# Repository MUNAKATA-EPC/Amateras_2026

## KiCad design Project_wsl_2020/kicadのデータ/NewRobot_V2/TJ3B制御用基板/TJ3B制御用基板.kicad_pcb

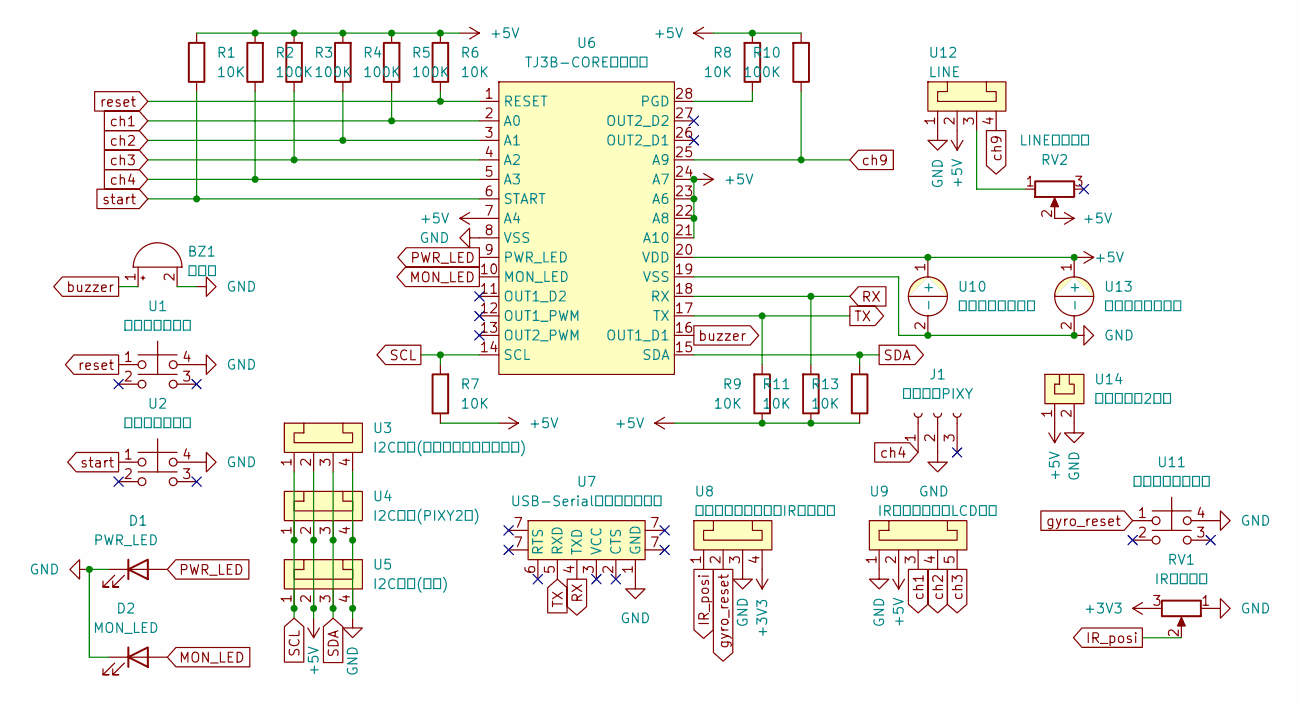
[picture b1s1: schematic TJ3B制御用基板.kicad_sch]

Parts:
BZ1: ブザー
D1: PWR_LED; PinSocket_1x02_P2.54mm_Vertical
D2: MON_LED; PinSocket_1x02_P2.54mm_Vertical
J1: カメラ用PIXY; PinSocket_1x03_P2.54mm_Vertical
R1, R6, R7, R8, R9, R11, R13: 10K; 抵抗
R2, R3, R4, R5, R10: 100K; 抵抗
RV1: IR可変抵抗; Potentiometer
RV2: LINE可変抵抗; Potentiometer
U1: リセットボタン; タクトスイッチ
U2: スタートボタン; タクトスイッチ
U3: I2Cピン(モータードライバー用); L字コネクター4ピン
U4: I2Cピン(PIXY2用); コネクター4ピン
U5: I2Cピン(予備); コネクター4ピン
U6: TJ3B-COREマイコン
U7: USB-Serial変換アダプター
U8: ジャイロリセット・IR可変抵抗; コネクター4ピン
U9: IR・ジャイロ・LCD基盤; L字コネクター5ピン
U10, U13: 電解コンデンサー
U11: ジャイロリセット; タクトスイッチ
U12: LINE; L字コネクター4ピン
U14: コネクター2ピン; L字コネクター2ピン

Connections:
+3V3: RV1.3, U8.4
+5V: R1.2, R2.2, R3.2, R4.2, R5.2, R6.2, R7.1, R8.2, R9.1, R10.2, R11.1, R13.1, RV2.2, U3.2, U4.2, U5.2, U6.7 (A4), U6.20 (VDD), U6.21 (A10), U6.22 (A8), U6.23 (A6), U6.24 (A7), U9.2, U10.1 (+), U12.2, U13.1 (+), U14.1
GND: BZ1.2 (+), D1.1 (K), D2.1 (K), J1.2, RV1.1, U1.4, U2.4, U3.4, U4.4, U5.4, U6.8 (VSS), U6.19 (VSS), U7.1 (GND), U8.3, U9.1, U10.2 (-), U11.4, U12.1, U13.2 (-), U14.2
IR_posi: RV1.2, U8.1
MON_LED: D2.2 (A), U6.10 (MON_LED)
unnamed: R8.1, U6.28 (PGD)
unnamed: RV2.1, U12.3
PWR_LED: D1.2 (A), U6.9 (PWR_LED)
RX: R11.2, U6.18 (RX), U7.4 (TXD)
SCL: R7.2, U3.1, U4.1, U5.1, U6.14 (SCL)
SDA: R13.2, U3.3, U4.3, U5.3, U6.15 (SDA)
TX: R9.2, U6.17 (TX), U7.5 (RXD)
buzzer: BZ1.1 (-), U6.16 (OUT1_D1)
ch1: R5.1, U6.2 (A0), U9.3
ch2: R4.1, U6.3 (A1), U9.4
ch3: R3.1, U6.4 (A2), U9.5
ch4: J1.1, R2.1, U6.5 (A3)
ch9: R10.1, U6.25 (A9), U12.4
gyro_reset: U8.2, U11.1
reset: R6.1, U1.1, U6.1 (RESET)
start: R1.1, U2.1, U6.6 (START)

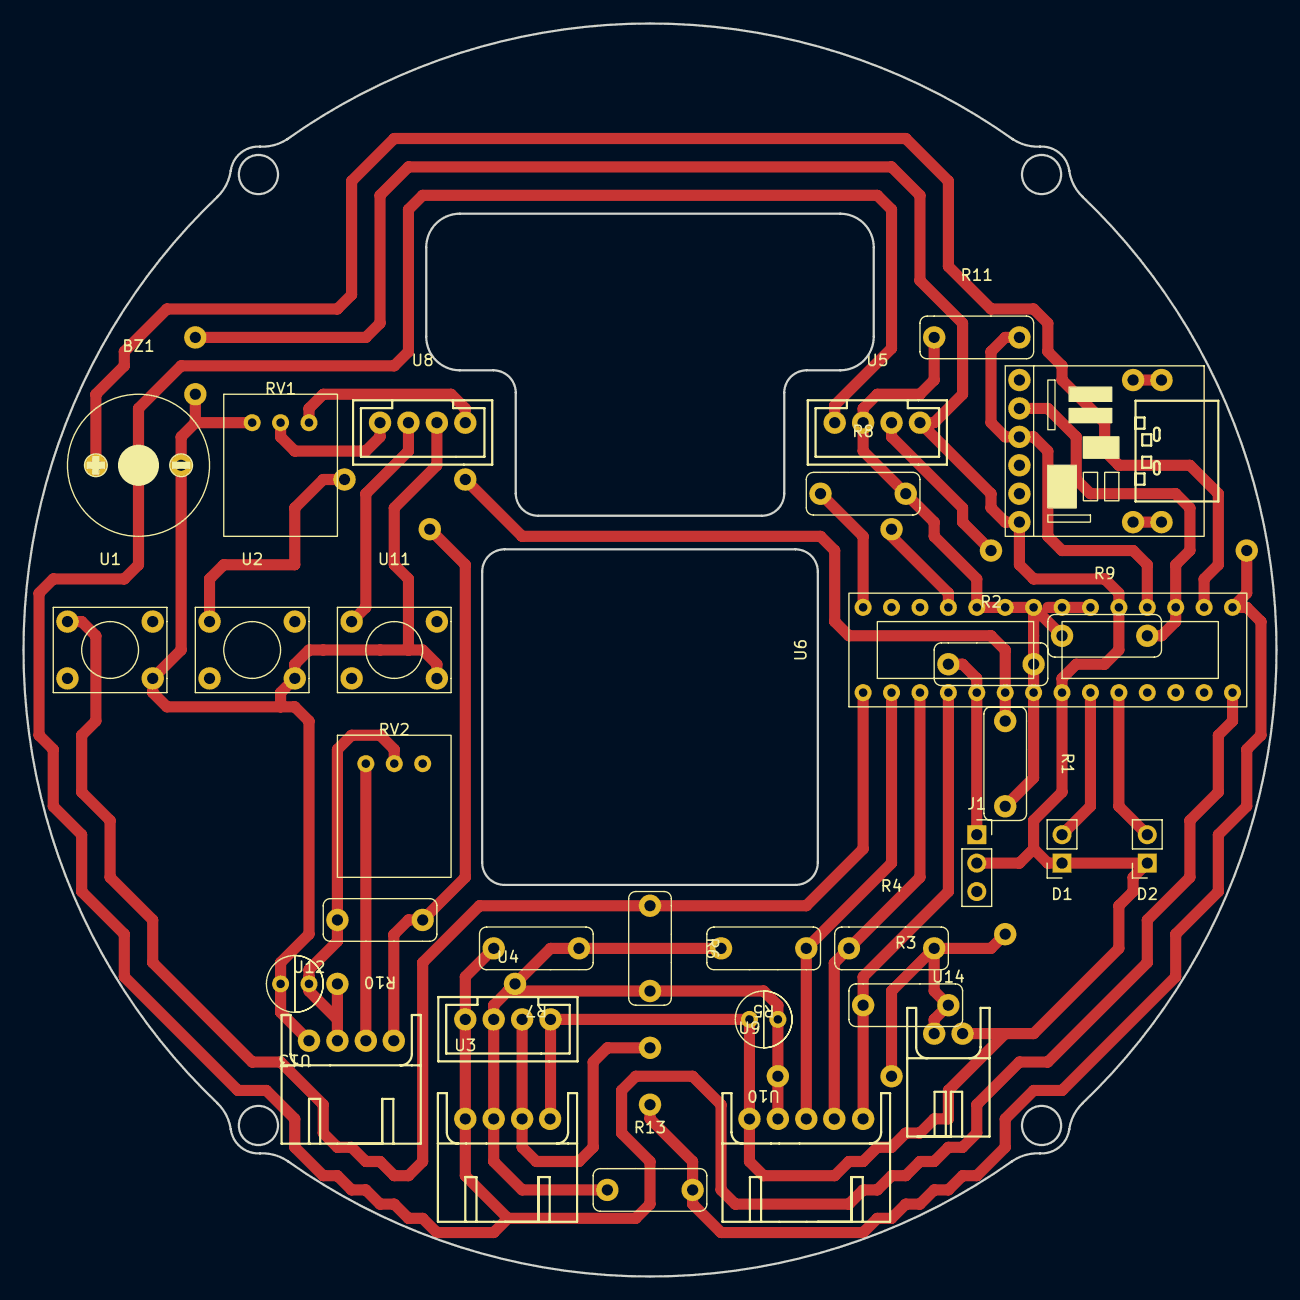
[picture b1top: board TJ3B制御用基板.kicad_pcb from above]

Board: 2 copper layers, 112.0 x 112.0 mm, 32 parts (0 on the bottom side), 21 nets.

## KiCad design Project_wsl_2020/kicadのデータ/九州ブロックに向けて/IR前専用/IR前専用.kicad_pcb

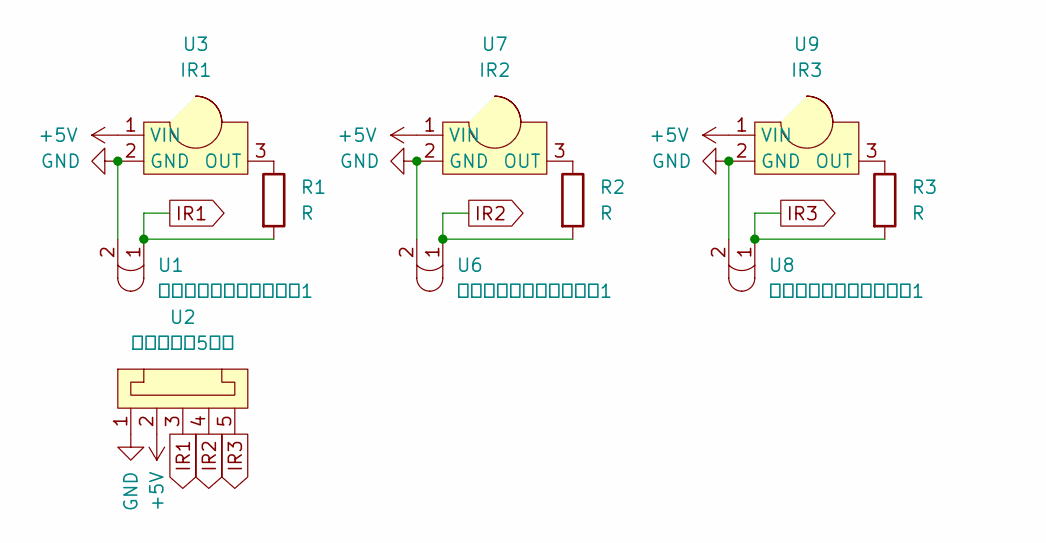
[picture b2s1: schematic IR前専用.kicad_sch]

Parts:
R1, R2, R3: R; 抵抗
U1, U6, U8: セラミックコンデンサー1; セラミックコンデンサー
U2: コネクター5ピン
U3: IR1; IR素子
U7: IR2; IR素子
U9: IR3; IR素子

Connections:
+5V: U2.2, U3.1 (VIN), U7.1 (VIN), U9.1 (VIN)
GND: U1.2, U2.1, U3.2 (GND), U6.2, U7.2 (GND), U8.2, U9.2 (GND)
IR1: R1.2, U1.1, U2.3
IR2: R2.2, U2.4, U6.1
IR3: R3.2, U2.5, U8.1
unnamed: R1.1, U3.3 (OUT)
unnamed: R2.1, U7.3 (OUT)
unnamed: R3.1, U9.3 (OUT)

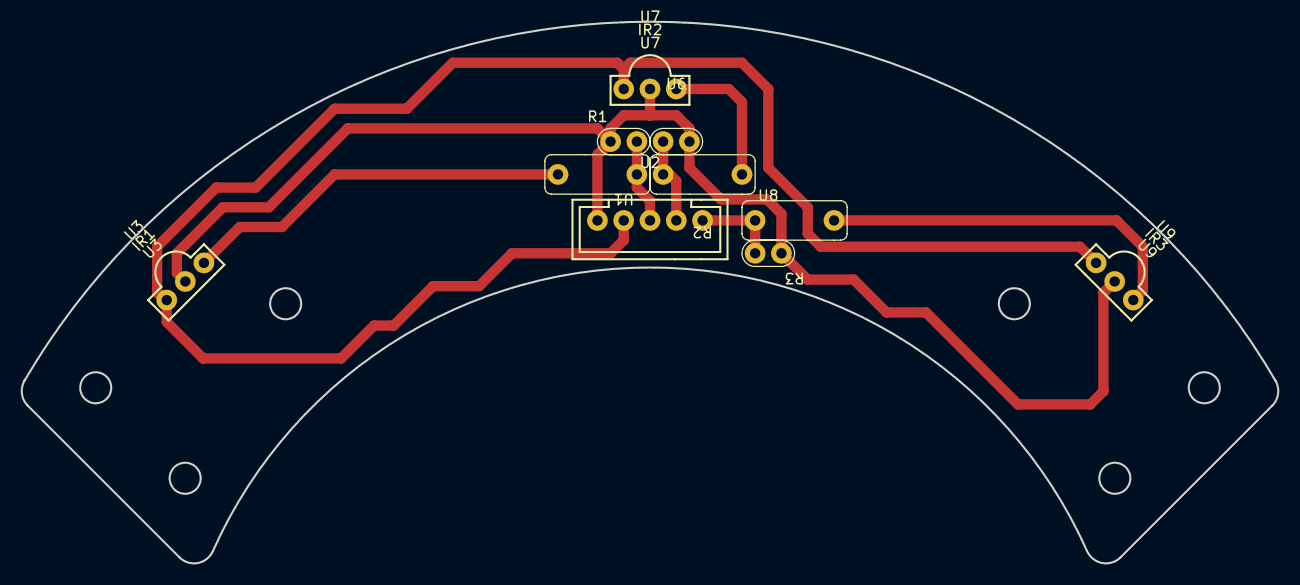
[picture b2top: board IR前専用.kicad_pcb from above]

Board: 2 copper layers, 121.4 x 52.3 mm, 10 parts (0 on the bottom side), 8 nets.

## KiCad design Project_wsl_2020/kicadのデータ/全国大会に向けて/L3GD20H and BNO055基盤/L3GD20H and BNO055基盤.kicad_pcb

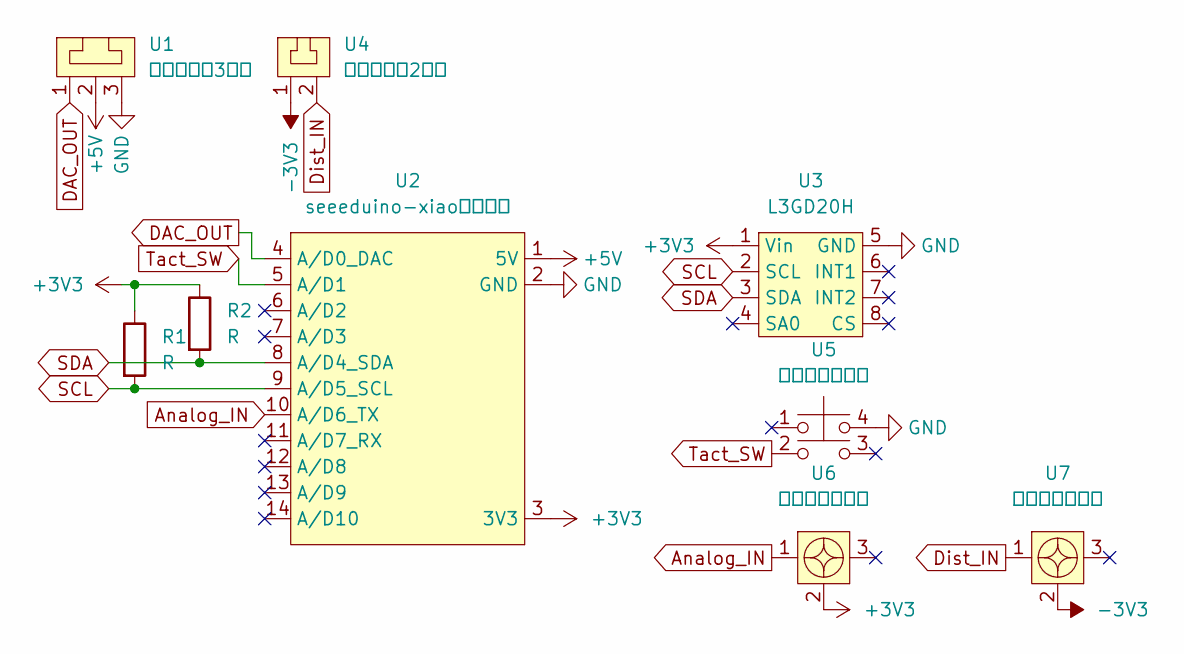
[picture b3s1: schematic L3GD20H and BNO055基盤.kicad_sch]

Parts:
R1, R2: R; 抵抗
U1: コネクター3ピン
U2: seeeduino-xiaoマイコン
U3: L3GD20H
U4: コネクター2ピン
U5: タクトスイッチ
U6, U7: ねじ式可変抵抗

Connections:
+3V3: R1.1, R2.1, U2.3 (3V3), U3.1 (Vin), U6.2
+5V: U1.2, U2.1 (5V)
-3V3: U4.1, U7.2
Analog_IN: U2.10 (A/D6_TX), U6.1
DAC_OUT: U1.1, U2.4 (A/D0_DAC)
Dist_IN: U4.2, U7.1
GND: U1.3, U2.2 (GND), U3.5 (GND), U5.4
SCL: R1.2, U2.9 (A/D5_SCL), U3.2 (SCL)
SDA: R2.2, U2.8 (A/D4_SDA), U3.3 (SDA)
Tact_SW: U2.5 (A/D1), U5.2

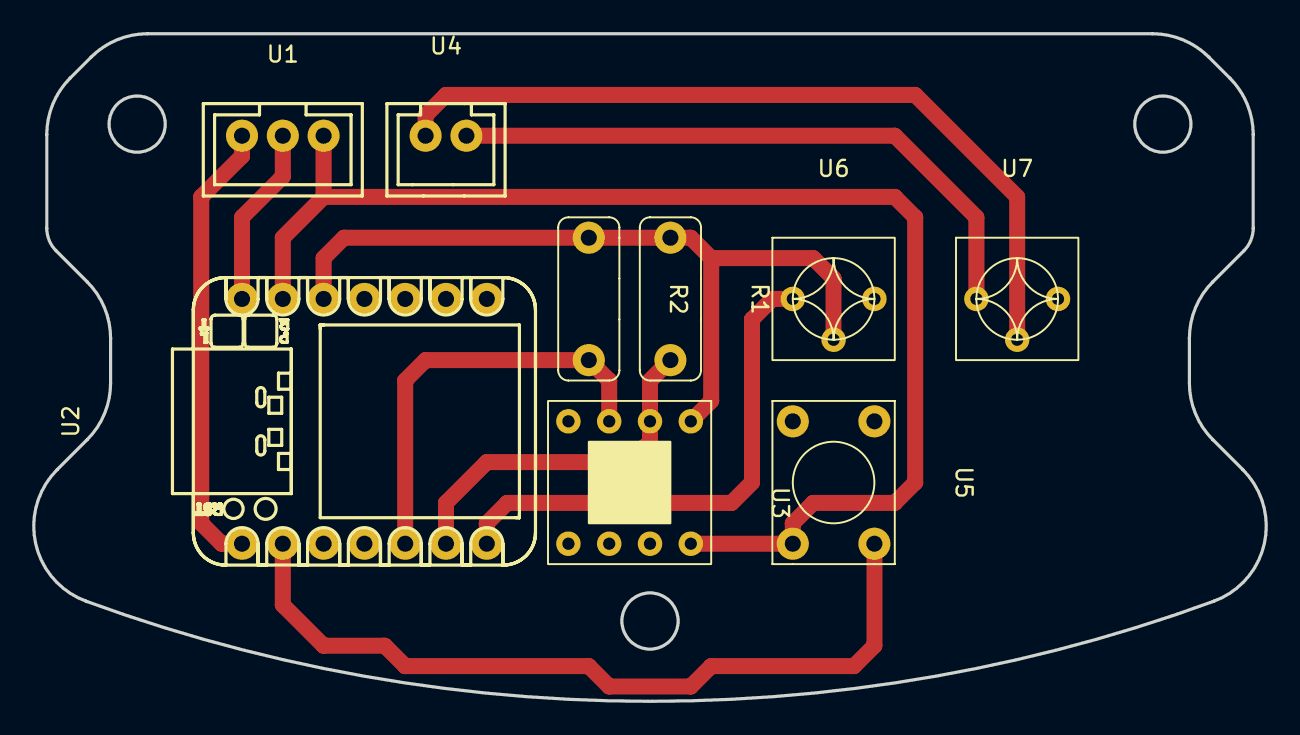
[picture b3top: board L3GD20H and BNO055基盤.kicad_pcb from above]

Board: 2 copper layers, 76.7 x 41.6 mm, 9 parts (0 on the bottom side), 10 nets.

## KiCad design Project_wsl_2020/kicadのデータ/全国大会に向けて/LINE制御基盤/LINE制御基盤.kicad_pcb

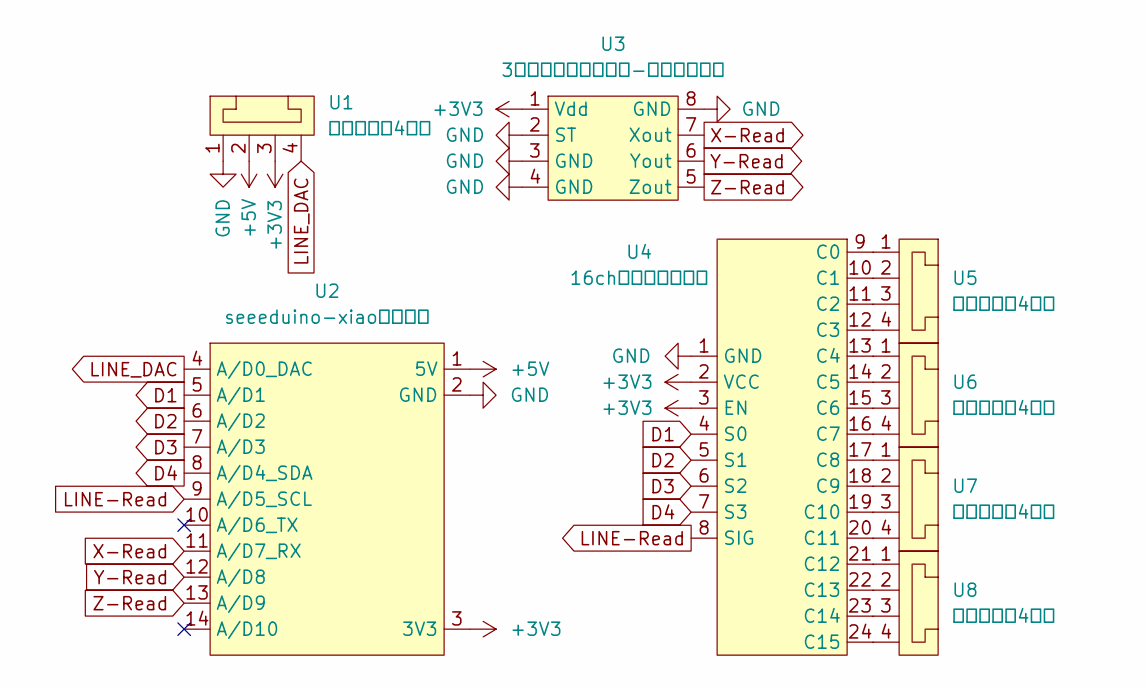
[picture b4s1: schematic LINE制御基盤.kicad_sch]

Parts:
U1, U5, U6, U7, U8: コネクター4ピン
U2: seeeduino-xiaoマイコン
U3: 3軸加速度モジュール-アナログ出力
U4: 16chマルチプレクサ; マルチプレクサ

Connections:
+3V3: U1.3, U2.3 (3V3), U3.1 (Vdd), U4.2 (VCC), U4.3 (EN)
+5V: U1.2, U2.1 (5V)
D1: U2.5 (A/D1), U4.4 (S0)
D2: U2.6 (A/D2), U4.5 (S1)
D3: U2.7 (A/D3), U4.6 (S2)
D4: U2.8 (A/D4_SDA), U4.7 (S3)
GND: U1.1, U2.2 (GND), U3.2 (ST), U3.3 (GND), U3.4 (GND), U3.8 (GND), U4.1 (GND)
LINE-Read: U2.9 (A/D5_SCL), U4.8 (SIG)
LINE_DAC: U1.4, U2.4 (A/D0_DAC)
unnamed: U4.9 (C0), U5.1
unnamed: U4.10 (C1), U5.2
unnamed: U4.11 (C2), U5.3
unnamed: U4.12 (C3), U5.4
unnamed: U4.13 (C4), U6.1
unnamed: U4.14 (C5), U6.2
unnamed: U4.15 (C6), U6.3
unnamed: U4.16 (C7), U6.4
unnamed: U4.17 (C8), U7.1
unnamed: U4.18 (C9), U7.2
unnamed: U4.19 (C10), U7.3
unnamed: U4.20 (C11), U7.4
unnamed: U4.21 (C12), U8.1
unnamed: U4.22 (C13), U8.2
unnamed: U4.23 (C14), U8.3
unnamed: U4.24 (C15), U8.4
X-Read: U2.11 (A/D7_RX), U3.7 (Xout)
Y-Read: U2.12 (A/D8), U3.6 (Yout)
Z-Read: U2.13 (A/D9), U3.5 (Zout)

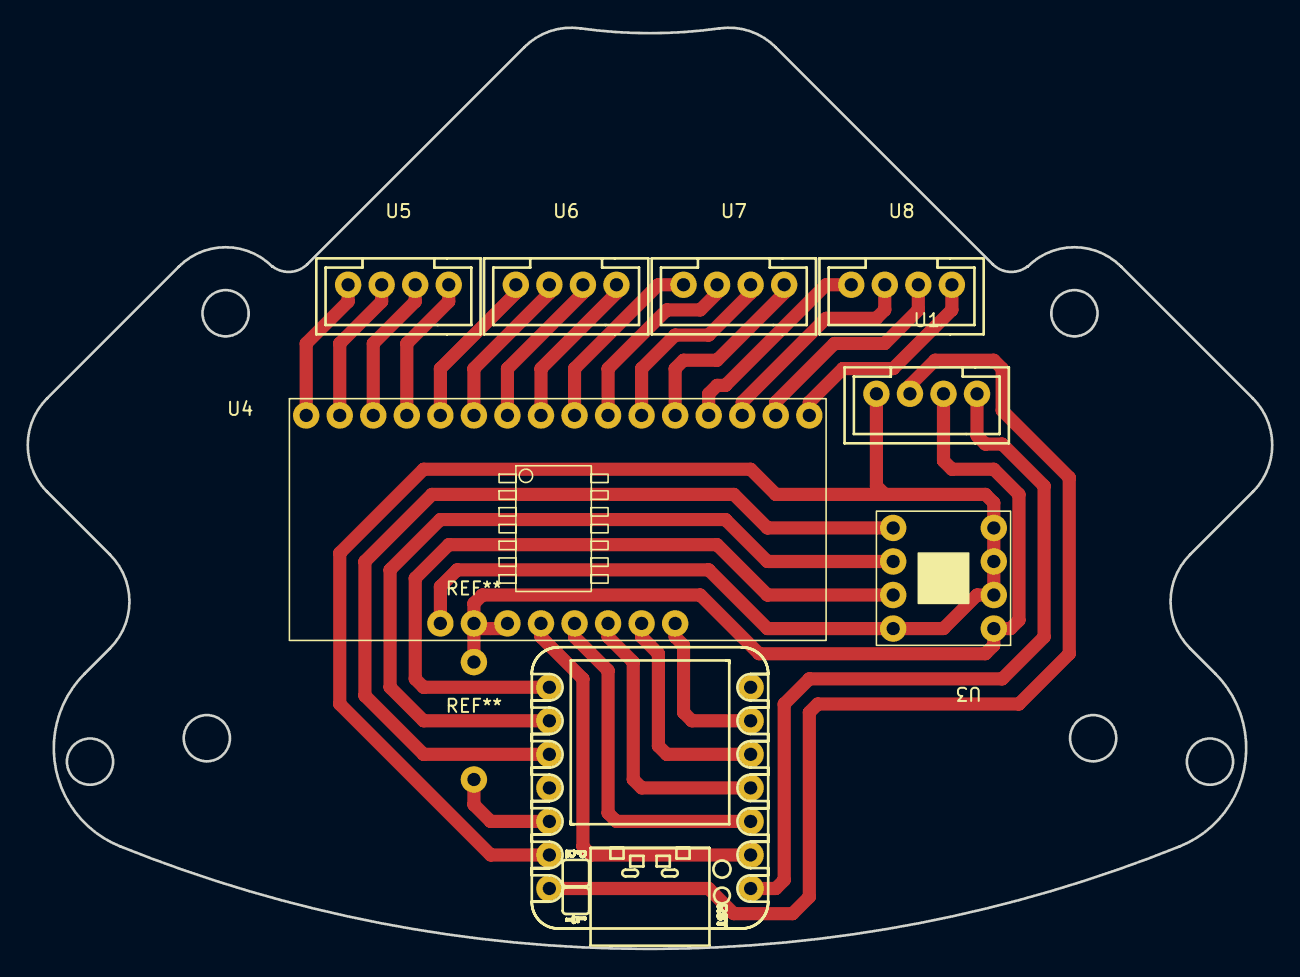
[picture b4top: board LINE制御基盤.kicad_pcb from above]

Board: 2 copper layers, 94.2 x 69.8 mm, 8 parts (0 on the bottom side), 28 nets.

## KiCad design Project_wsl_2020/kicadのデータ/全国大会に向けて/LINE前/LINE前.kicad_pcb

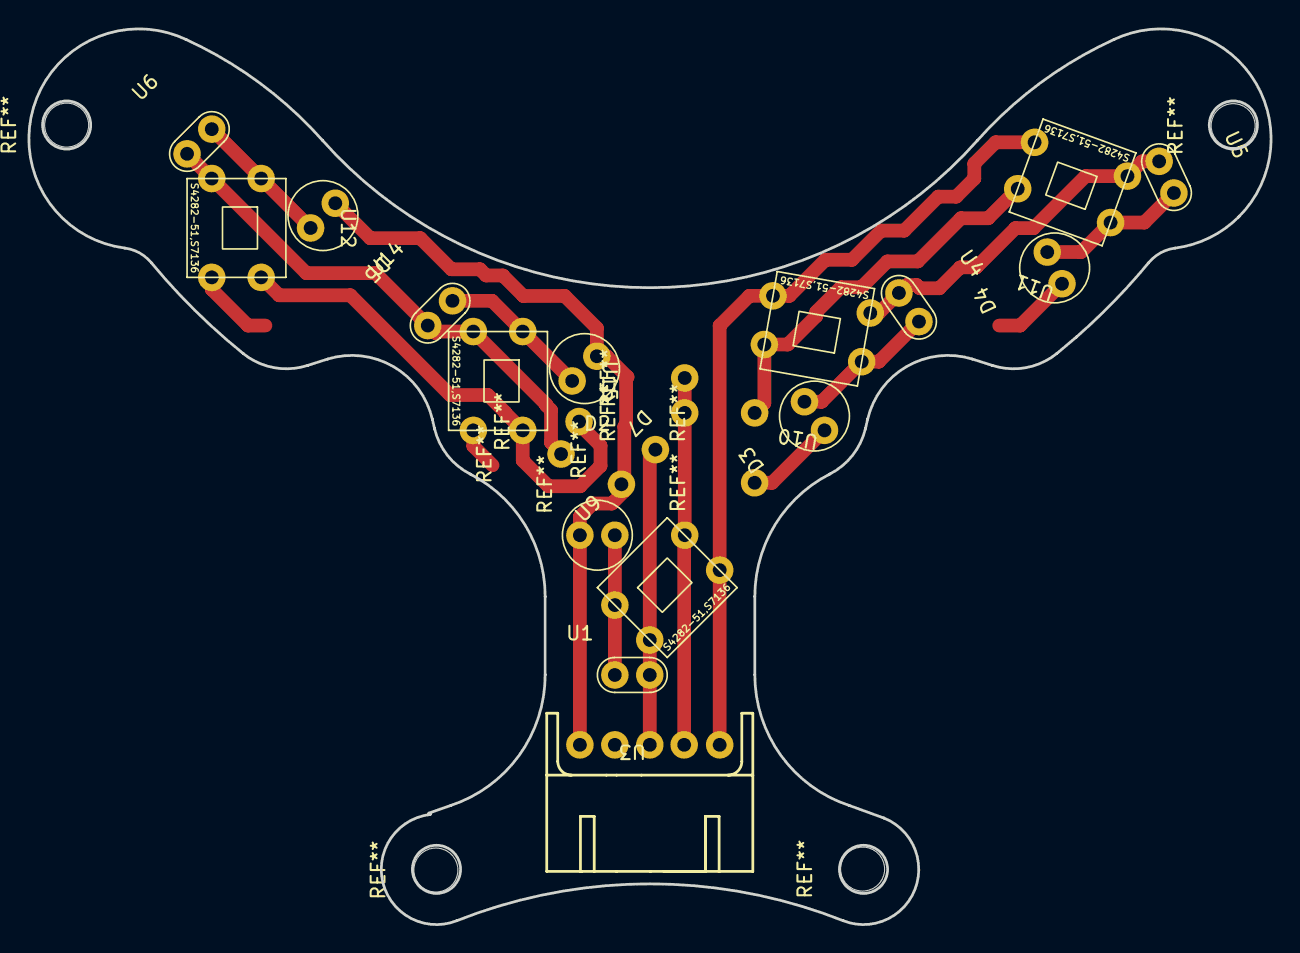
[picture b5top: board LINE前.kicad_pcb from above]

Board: 2 copper layers, 90.3 x 65.1 mm, 16 parts (0 on the bottom side), 9 nets.

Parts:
D2, D3, D4, D5, D7: LED
U1: コネクター5ピン; L字コネクター5ピン
U3, U4, U5, U6, U14: セラミックコンデンサー
U9: S1; S4282-51,S7136
U10: S2; S4282-51,S7136
U11: S3; S4282-51,S7136
U12, U15: S0; S4282-51,S7136

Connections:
+5V: U1.3, U3.1, U4.1, U5.1, U6.1, U9.2 (Vcc), U10.2 (Vcc), U11.2 (Vcc), U12.2 (Vcc), U14.1, U15.2 (Vcc)
GND: U1.4, U9.4 (GND), U10.4 (GND), U11.4 (GND), U12.4 (GND), U15.4 (GND)
LINE_LED: D2.1 (K), D3.1 (K), D4.1 (K), D5.1 (K), D7.1 (K), U1.1
LINE_data: U1.5, U9.3 (Vout), U10.3 (Vout), U11.3 (Vout), U12.3 (Vout), U15.3 (Vout)
unnamed: D2.2 (A), U3.2, U9.1 (cathode)
unnamed: D3.2 (A), U4.2, U10.1 (cathode)
unnamed: D4.2 (A), U5.2, U11.1 (cathode)
unnamed: D5.2 (A), U6.2, U12.1 (cathode)
unnamed: D7.2 (A), U14.2, U15.1 (cathode)

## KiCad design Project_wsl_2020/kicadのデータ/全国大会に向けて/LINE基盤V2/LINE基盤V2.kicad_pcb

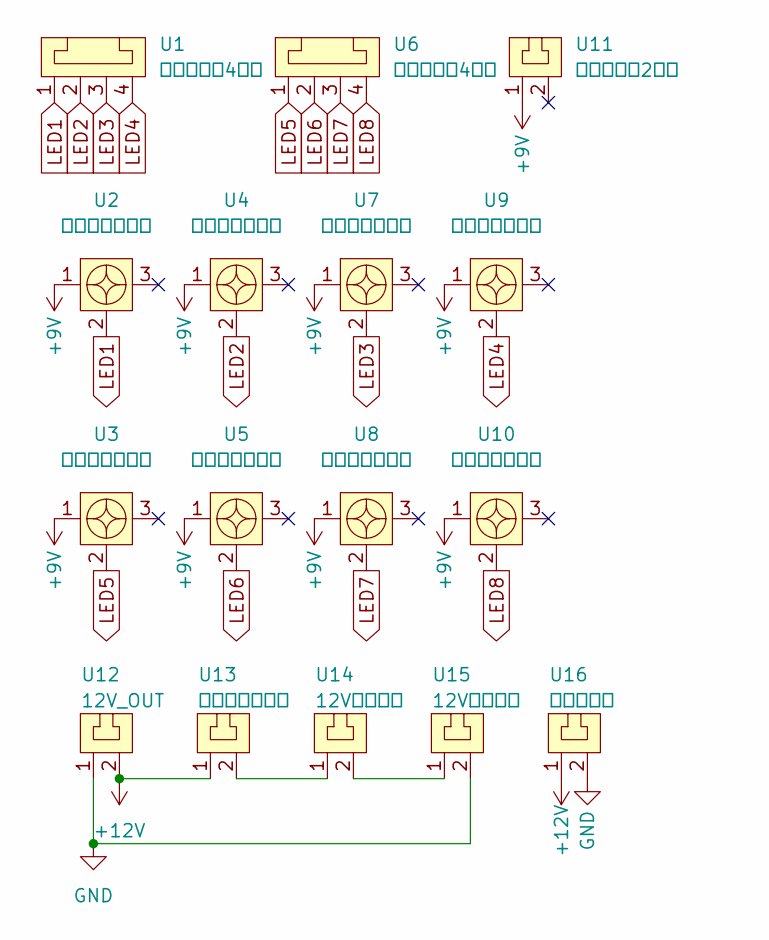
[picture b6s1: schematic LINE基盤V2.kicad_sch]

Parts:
U1, U6: コネクター4ピン
U2, U3, U4, U5, U7, U8, U9, U10: ねじ式可変抵抗
U11: コネクター2ピン
U12: 12V_OUT; コネクター2ピン
U13: トグルスイッチ; コネクター2ピン
U14, U15: 12Vスナップ; コネクター2ピン
U16: ターミナル; コネクター2ピン

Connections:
+9V: U2.1, U3.1, U4.1, U5.1, U7.1, U8.1, U9.1, U10.1, U11.1
+12V: U12.2, U13.1, U16.1
GND: U12.1, U15.2, U16.2
LED1: U1.1, U2.2
LED2: U1.2, U4.2
LED3: U1.3, U7.2
LED4: U1.4, U9.2
LED5: U3.2, U6.1
LED6: U5.2, U6.2
LED7: U6.3, U8.2
LED8: U6.4, U10.2
unnamed: U13.2, U14.1
unnamed: U14.2, U15.1

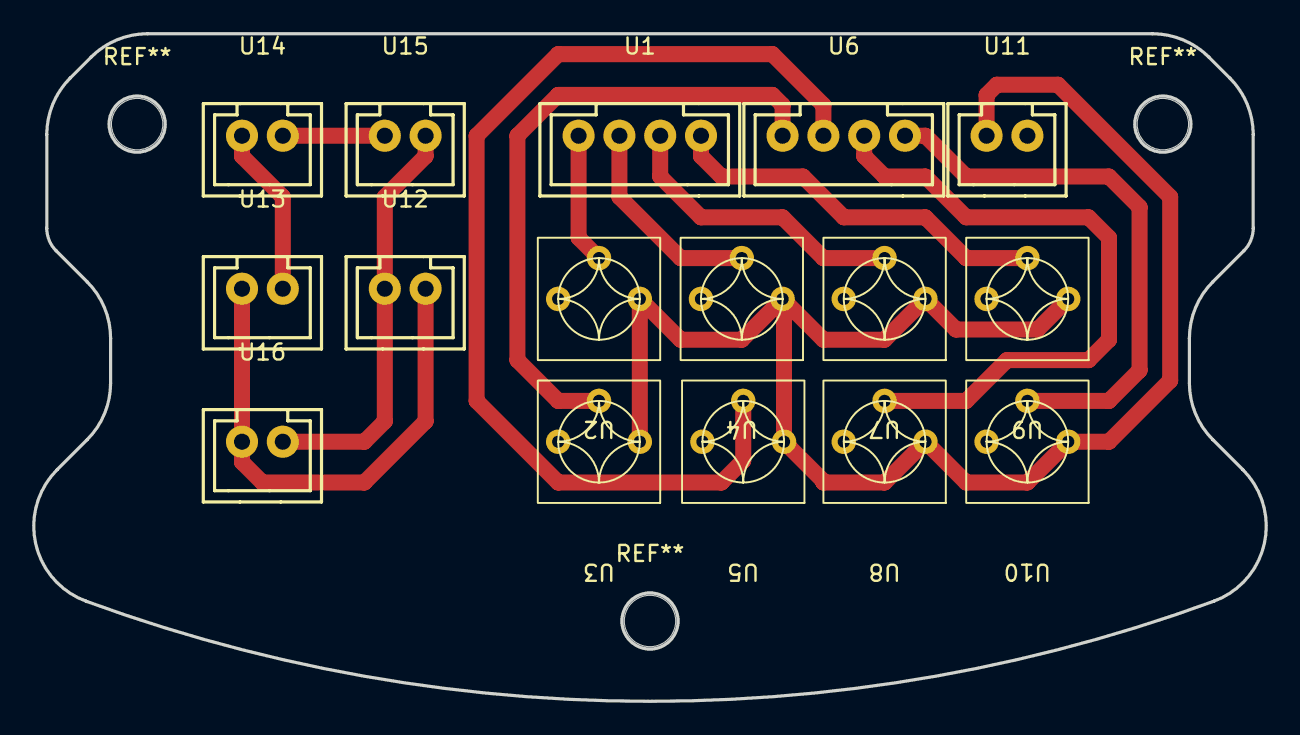
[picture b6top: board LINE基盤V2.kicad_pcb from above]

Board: 2 copper layers, 76.7 x 41.6 mm, 16 parts (0 on the bottom side), 13 nets.

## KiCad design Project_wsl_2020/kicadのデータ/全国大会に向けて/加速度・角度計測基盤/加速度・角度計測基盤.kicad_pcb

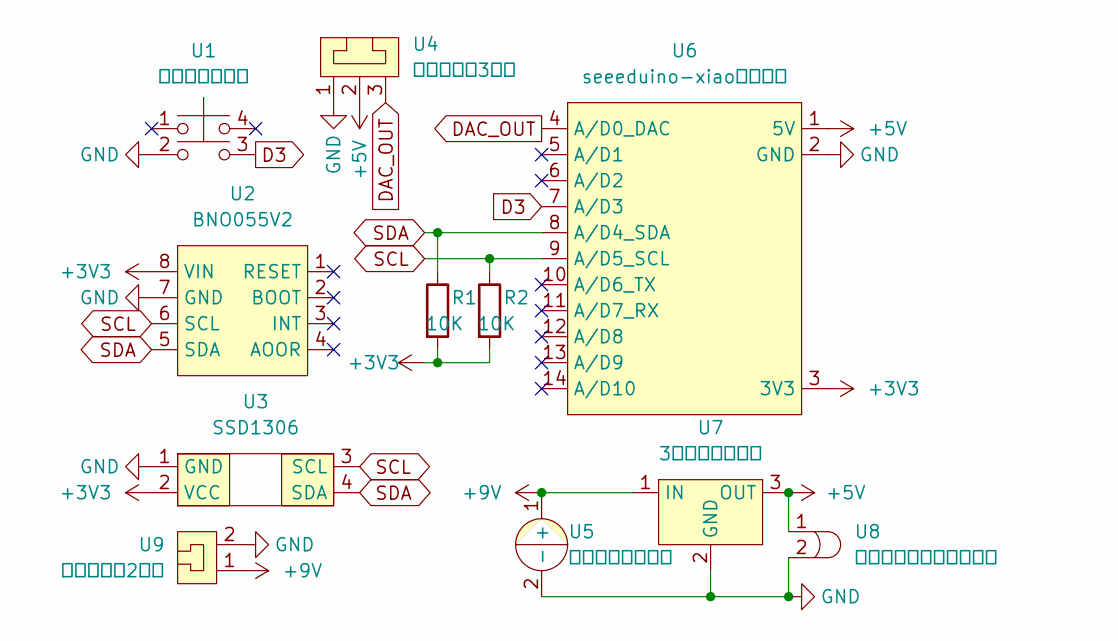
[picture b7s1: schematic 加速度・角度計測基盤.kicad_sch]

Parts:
R1, R2: 10K; 抵抗
U1: タクトスイッチ
U2: BNO055V2
U3: SSD1306
U4: コネクター3ピン; L字コネクター3ピン
U5: 電解コンデンサー
U6: seeeduino-xiaoマイコン
U7: 3端子レギュレタ; 3端子レギュレーター
U8: セラミックコンデンサー
U9: コネクター2ピン

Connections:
+3V3: R1.2, R2.2, U2.8 (VIN), U3.2 (VCC), U6.3 (3V3)
+5V: U4.2, U6.1 (5V), U7.3 (OUT), U8.1
+9V: U5.1 (+), U7.1 (IN), U9.1
D3: U1.3, U6.7 (A/D3)
DAC_OUT: U4.3, U6.4 (A/D0_DAC)
GND: U1.2, U2.7 (GND), U3.1 (GND), U4.1, U5.2 (-), U6.2 (GND), U7.2 (GND), U8.2, U9.2
SCL: R2.1, U2.6 (SCL), U3.3 (SCL), U6.9 (A/D5_SCL)
SDA: R1.1, U2.5 (SDA), U3.4 (SDA), U6.8 (A/D4_SDA)

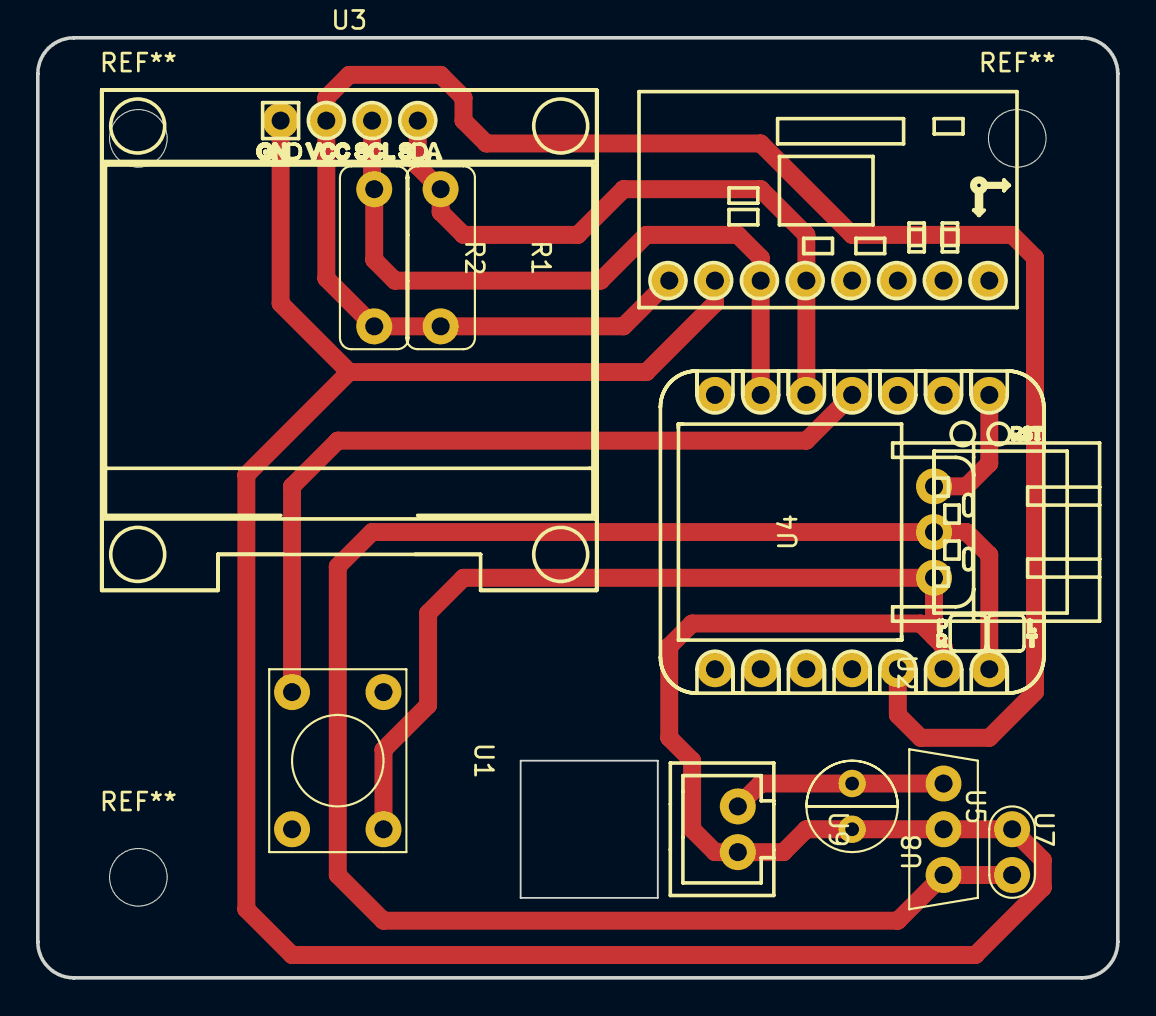
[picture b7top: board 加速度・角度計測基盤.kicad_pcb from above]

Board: 2 copper layers, 60.0 x 52.2 mm, 11 parts (0 on the bottom side), 8 nets.
